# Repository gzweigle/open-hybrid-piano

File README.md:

# Hybrid MIDI Digital Piano

Also known as **stem piano**

## How to Build A Hybrid Piano
Go straight to the [pianos/](pianos/) directory!

But first, please read the [WARNINGS](WARNINGS.md) and [HELP](HELP.md) files that are located in this root directory.

See the [STATUS](STATUS.md) file for status of the project and repository.

If you would like to contribute hardware, software, mechanical, or firmware to the project, see the [CONTRIBUTING](CONTRIBUTING.md) file.

**If you build a piano, please share about it in the Show & Tell Discussions of this repository.**

## Overview

A hybrid piano combines the physical action of an acoustic piano with MIDI, sound generation, and other features of a digital keyboard. Some piano manufacturers sell hybrid pianos.

This project ("*stem piano*") is an open-source hybrid digital piano.

The qualifier digital is important. It means that signals are sampled with an analog-to-digital converter (ADC) and then all processing is with a microprocessor. Therefore, once the hardware is installed all algorithms, improvements, and new features are with software or firmware.

The repository includes schematics, printed circuit board layouts, firmware source files for the real-time processing, optional software source files for Ethernet connected features, and lists of required hardware components.

A physical piano action, or other instrument, is required. The electronics and code (*stem piano*) will work with a grand or upright piano action. Mechanical suggestions are included but not detailed mechanical instructions.

The platform and code could also adapt to building a range of other unique and innovative musical instruments.

## Directory Organization

The components required to build a piano are located in the [firmware/](firmware/), [hardware/](hardware/), [mechanical/](mechanical/) and [software/](software/) directories. In each directory is a *research* subdirectory and a *releases* subdirectory.

Each *research* subdirectory contains code and hardware for work in progress. It could have major bugs. It could be incomplete.

Each *releases* subdirectory contains code and hardware ready for use. The material in *releases* could partially duplicate material in one or more *research* subdirectories. However, the requirement is that anything in *releases* is well-tested, complete, and ready-to-use.

More details on each directory:

#### [design/](design/)

Designs and engineering analysis. To keep the repository small, associated data may be located in the separate Piano-Data repository.

#### [documentation/](documentation/)

High level documentation.

Includes [documentation/video_documentation.md](documentation/video_documentation.md) for historical, how-to, and other documentation in video form.

#### [pianos/](pianos/)

Building a complete piano requires firmware, hardware, mechanical, and sometimes software. The *pianos/* directory provides information on everything needed to build a specific version of a musical instrument.

Best place to start for learning the firmware, software, mechanical, and hardware.

#### [firmware/](firmware/)

Real-time code running on custom hardware from *hardware/* directory.

#### [hardware/](hardware/)

All printed circuit boards and related parts and design. A separate open-source license for the hardware is in this directory and applies to all hardware.

#### [mechanical/](mechanical/)

Anything to physically build a piano. A separate open-source license for mechanical is in this directory and applies to anything mechanical.

#### [software/](software/)

Code running on a standard computer or Raspberry Pi connected to the piano over Ethernet or MIDI.

## Repositories

#### (1) Original

This "DIY" repository. Organized per above.

#### (2) Stem Piano

https://github.com/stem-piano

Experimenting with a GitHub organization. The documentation and links for building individual pianos is here. Links are back to this original "DIY" repository.

May or may not migrate all files in the future. To be decided in the future.

## Related Projects:

Work was inspired, in part, by https://github.com/ekumanov/cybrid

See also:

* https://github.com/jkominek/piano-conversion/
* https://github.com/davidedelvento/Mybrid
* https://www.youtube.com/watch?v=nRBsudMpwwc
* https://www.youtube.com/watch?v=-kpf0OSJxkE
* https://www.youtube.com/watch?v=b-PRGymqECM

## "stem piano" because?

* science technology engineering math
* like a plant stem, everything here is one component of the overall instrument
* like a note stem, everything here is one component of...
* 12 leaves on the logo, matches 12 piano notes
* logo looks like a sine wave
* sounds cool
* does not sound cool

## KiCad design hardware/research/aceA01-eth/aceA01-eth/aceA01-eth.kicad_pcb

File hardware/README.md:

# Stem Piano Hardware
See [kicad_general.md](./kicad_general.md) in this directory for information on the libraries.

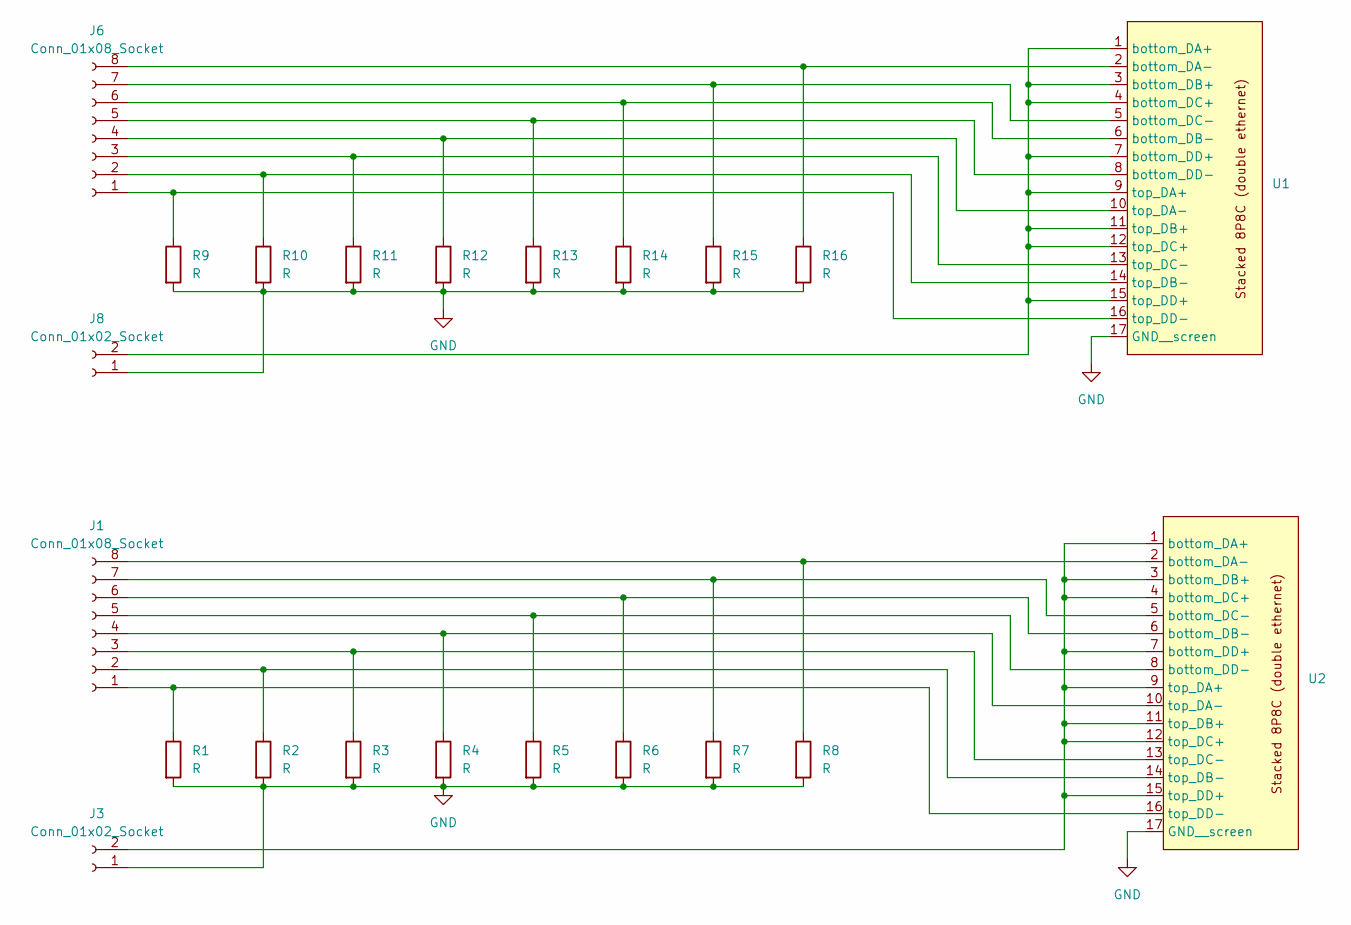
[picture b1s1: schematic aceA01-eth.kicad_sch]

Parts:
J1: Conn_01x08_Socket; PinSocket_1x08_P2.54mm_Vertical
J3, J8: Conn_01x02_Socket; PinSocket_1x02_P2.54mm_Vertical_SMD_Pin1Right
J6: Conn_01x08_Socket; PinSocket_1x08_P2.54mm_Vertical_SMD_Pin1Left
R1, R2, R3, R4, R5, R6, R7, R8, R9, R10, R11, R12, R13, R14, R15, R16: R; R_0805_2012_1.20x1.40mm_medpad
U1: Stacked8P8C_noFrontPins
U2: Stacked8P8C

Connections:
GND: J3.1, J8.1, R1.2, R2.2, R3.2, R4.2, R5.2, R6.2, R7.2, R8.2, R9.2, R10.2, R11.2, R12.2, R13.2, R14.2, R15.2, R16.2, U1.17 (GND__screen), U2.17 (GND__screen)
unnamed: J1.1, R1.1, U2.16 (top_DD-)
unnamed: J1.2, R2.1, U2.14 (top_DB-)
unnamed: J1.3, R3.1, U2.13 (top_DC-)
unnamed: J1.4, R4.1, U2.10 (top_DA-)
unnamed: J1.5, R5.1, U2.8 (bottom_DD-)
unnamed: J1.6, R6.1, U2.6 (bottom_DB-)
unnamed: J1.7, R7.1, U2.5 (bottom_DC-)
unnamed: J1.8, R8.1, U2.2 (bottom_DA-)
unnamed: J3.2, U2.1 (bottom_DA+), U2.3 (bottom_DB+), U2.4 (bottom_DC+), U2.7 (bottom_DD+), U2.9 (top_DA+), U2.11 (top_DB+), U2.12 (top_DC+), U2.15 (top_DD+)
unnamed: J6.1, R9.1, U1.16 (top_DD-)
unnamed: J6.2, R10.1, U1.14 (top_DB-)
unnamed: J6.3, R11.1, U1.13 (top_DC-)
unnamed: J6.4, R12.1, U1.10 (top_DA-)
unnamed: J6.5, R13.1, U1.8 (bottom_DD-)
unnamed: J6.6, R14.1, U1.6 (bottom_DB-)
unnamed: J6.7, R15.1, U1.5 (bottom_DC-)
unnamed: J6.8, R16.1, U1.2 (bottom_DA-)
unnamed: J8.2, U1.1 (bottom_DA+), U1.3 (bottom_DB+), U1.4 (bottom_DC+), U1.7 (bottom_DD+), U1.9 (top_DA+), U1.11 (top_DB+), U1.12 (top_DC+), U1.15 (top_DD+)

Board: 2 copper layers, 22 parts (20 on the bottom side), 19 nets, no tracks yet.

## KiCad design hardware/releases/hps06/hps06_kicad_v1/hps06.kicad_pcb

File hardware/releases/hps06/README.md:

# Hammer Position Sensor (HPS) Version 0.6

## Introduction

Originally, the HPS PCB was for hammers.  However, the sensor also works for dampers.  Not changing the name because many circuit boards have already been built.

This circuit board includes a trimming resistor. Unless needed for a specific use case, the circuit board with trimming resistor is not recommended.

In repository for historical reasons.

## Features

### I/O
* Power input.
* Analog output signal, with range set by resistors.
* Ground.

### Size
* 1.5 inches long.
* 0.4 inches wide.

### Capabilities
* CNY70 sensor.
* Trimming resistor to fine tune output voltage maximum value.
* All resistors are surface mount packages.

### Pin Order:
* Power
* Signal
* Ground

## Calibrating

Adjust the RV0 trimming resistor to get the output voltage in the correct range. A 1.0mm flathead screwdriver is required. Turn the screw slowly and gently. Information according to the datasheet [Bourns 3224 - 4mm SMD Trimpot Trimming Potentiometer, C1753 5/17/18]:
* Adjustment angle = 12 turns.
* Rotational cycling max = 200 cycles.

Based on testing, typical adjustment is no more than approximately 2 turns clockwise or counterclockwise. This results in a resistance range of approximately 75 to 125 ohms.

Turning the RV0 trimming screw clockwise decreases the resistance between pins 2 and 3 of the trimming resistor RV0 ==> this decreases the combined resistance R1 + RV0 ==> this increases the forward current of the CNY-70 emitter ==> this increases the output voltage.

Turning the RV0 trimming screw counterclockwise increases the resistance between pins 2 and 3 of the trimming resistor RV0 ==> this increases the combined resistance R1 + RV0 ==> this decreases the forward current of the CNY-70 emitter ==> this decreases the output voltage.

R2 sets the maximum output voltage. If the output voltage is too large, the analog-to-digital converter will clip. If the output voltage is smaller, it decreases the dynamic range. The piano will work with a lower dynamic range but may not work if the signal is clipping. Therefore, if the R2 value in bill of materials is unavailable, choose a smaller value.

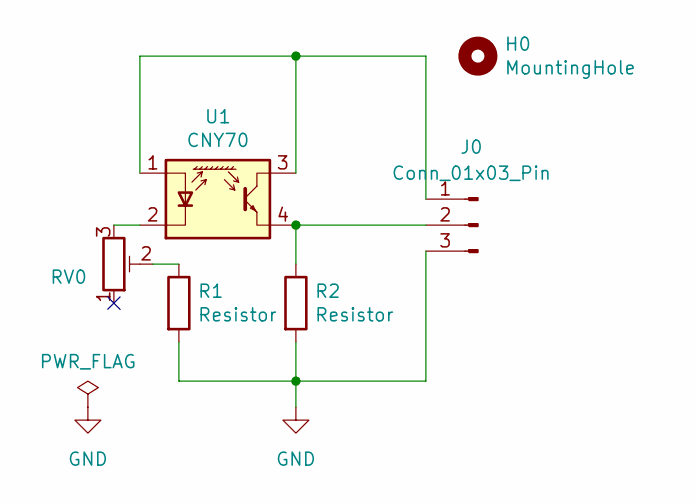
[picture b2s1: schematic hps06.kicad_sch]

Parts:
H0: MountingHole; MountingHole_3.5mm_Pad_TopBottom
J0: Conn_01x03_Pin; PinHeader_1x03_P2.54mm_Vertical
R1, R2: Resistor; R_0805_2012_1.20x1.40mm_bigpad
RV0: R_Potentiometer_Trim; Bourns_3224X_Vertical_bigpads
U1: CNY70; Vishay_CNY70

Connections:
GND: J0.3, R1.2, R2.2
unnamed: J0.1, U1.1 (A), U1.3 (C)
unnamed: J0.2, R2.1, U1.4 (E)
unnamed: R1.1, RV0.2
unnamed: RV0.3, U1.2 (K)

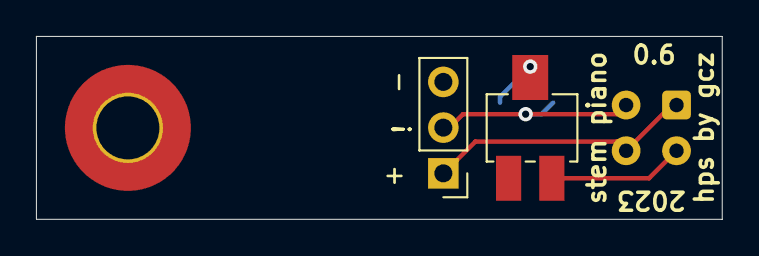
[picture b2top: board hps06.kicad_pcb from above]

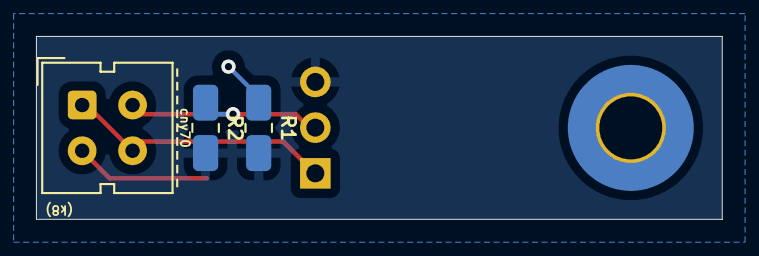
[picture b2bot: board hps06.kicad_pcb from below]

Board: 2 copper layers, 38.1 x 10.2 mm, 6 parts (3 on the bottom side), 5 nets.

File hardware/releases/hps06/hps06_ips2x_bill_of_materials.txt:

Label,   Description,           Package,    Part Number,          Required?,     Est Cost,     Comment
-,       HPS 0.6 circuit board, -,          -,                    Yes,           1.00,        -
RV0,     Trimmer, 200 ohm,      -,          3224X-1-201E,         Yes,           5.00,        -
R1,      50 ohm resistor,       0805,       CRCW080550R0FKTA,     Yes,           0.25,        0.125W. 5% tolerance or better. On back of PCB.
R2,      4120 ohm resistor,     0805,       ERA-6AEB4121V,        Yes,           0.25,        0.125W. 5% tolerance or better. On back of PCB.
U1,      CNY70 optical sensor,  -,          CNY70,                Yes,           1.00,        On back of PCB.
J0,      1x3 pin male 0.1in,    -,          -,                    Yes,           0.06,        -

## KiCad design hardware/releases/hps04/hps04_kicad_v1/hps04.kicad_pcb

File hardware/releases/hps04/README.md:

# Hammer Position Sensor (HPS) Version 0.4

## Introduction

Originally, the HPS PCB was for hammers.  However, the sensor also works for dampers.  Not changing the name because many circuit boards have already been built.

## Features

### I/O
* Power input.
* Analog output signal, with range set by resistors.
* Ground.

### Size
* 1.5 inches long.
* 0.4 inches wide.

### Capabilities
* CNY70 sensor.
* Fixed resistors.
* All resistors are through hole.

### Pin Order:
* Power
* Signal
* Ground

## Resistors

R2 sets the maximum output voltage. If the output voltage is too large, the analog-to-digital converter will clip. If the output voltage is smaller, it decreases the dynamic range. The piano works with a lower dynamic range but may not work if the signal is clipping. Therefore, if the R2 value in bill of materials is unavailable, choose a smaller value. If the R1 value is unavailable, choose a larger value.

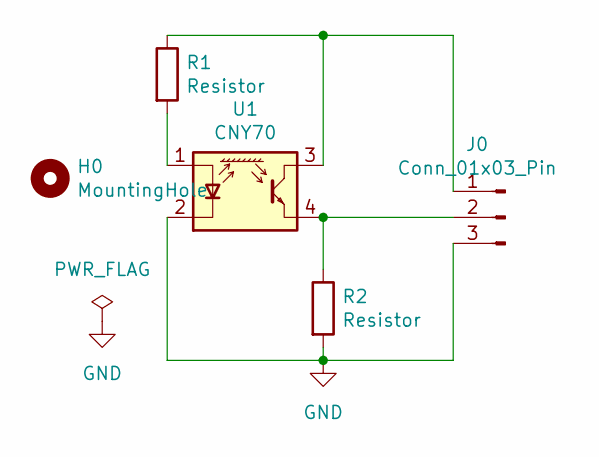
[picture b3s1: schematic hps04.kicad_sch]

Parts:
H0: MountingHole; MountingHole_3.5mm_Pad_TopBottom
J0: Conn_01x03_Pin; PinHeader_1x03_P2.54mm_Vertical
R1, R2: Resistor; R_Axial_DIN0204_L3.6mm_D1.6mm_P7.62mm_Horizontal
U1: CNY70; Vishay_CNY70

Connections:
GND: J0.3, R2.2, U1.2 (K)
unnamed: J0.1, R1.1, U1.3 (C)
unnamed: J0.2, R2.1, U1.4 (E)
unnamed: R1.2, U1.1 (A)

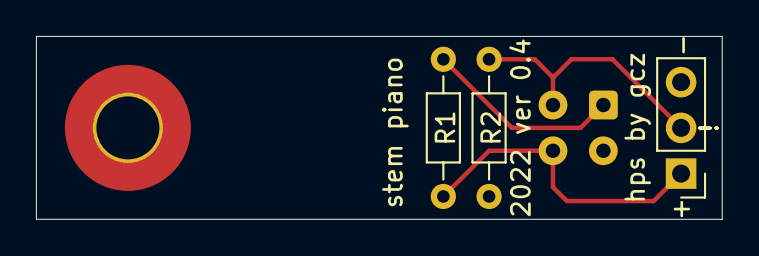
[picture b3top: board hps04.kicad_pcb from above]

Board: 2 copper layers, 38.1 x 10.2 mm, 5 parts (1 on the bottom side), 4 nets.

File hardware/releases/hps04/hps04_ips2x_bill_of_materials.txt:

Label,   Description,           Package,       Part Number,      Required?,     Est Cost,     Comment
-,       HPS 0.4 circuit board, -,             -,                Yes,           1.00,        -
R1,      50 ohm resistor,       through hole,  -,                Yes,           0.05,        0.125W. 5% tolerance or better.
R2,      4100 ohm resistor,     through hole,  -,                Yes,           0.05,        This value or slightly smaller.
U1,      CNY70 optical sensor,  -,             CNY70,            Yes,           1.00,        -
J0,      1x3 pin male 0.1in,    -,             -,                Yes,           0.06,        -

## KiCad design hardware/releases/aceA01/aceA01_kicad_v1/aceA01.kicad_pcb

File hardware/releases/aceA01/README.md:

# Analog Condition Equalize (ACE) "A" - Version 0.1

Identical to ACE A 0.0 with the following changes:
* Removed ground plane because it makes soldering more difficult (thermal) and adds little benefit.
* For headers placed on back of board, corrected the footprints to match.
* Adjusted some of the footprint label locations.

No functional changes.

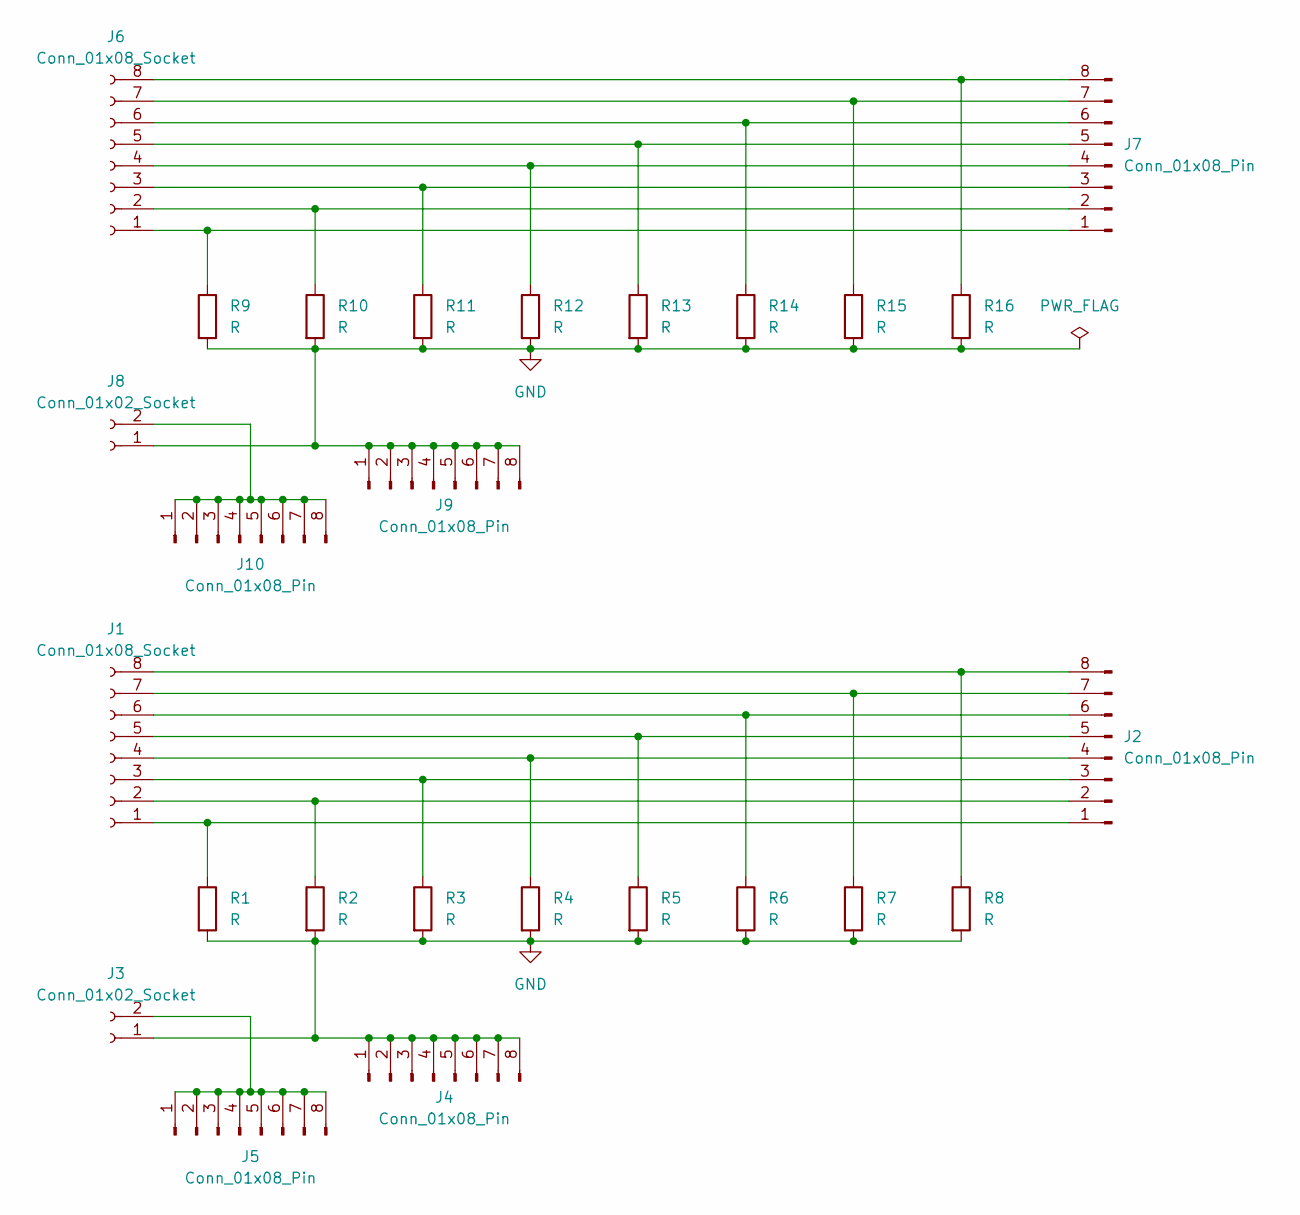
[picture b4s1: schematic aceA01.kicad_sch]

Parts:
J1, J6: Conn_01x08_Socket; PinSocket_1x08_P2.54mm_Vertical
J2, J4, J5, J7, J9, J10: Conn_01x08_Pin; PinHeader_1x08_P2.54mm_Vertical
J3, J8: Conn_01x02_Socket; PinSocket_1x02_P2.54mm_Vertical
R1, R2, R3, R4, R5, R6, R7, R8, R9, R10, R11, R12, R13, R14, R15, R16: R; R_0805_2012_1.20x1.40mm_medpad

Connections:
GND: J3.1, J4.1, J4.2, J4.3, J4.4, J4.5, J4.6, J4.7, J4.8, J8.1, J9.1, J9.2, J9.3, J9.4, J9.5, J9.6, J9.7, J9.8, R1.2, R2.2, R3.2, R4.2, R5.2, R6.2, R7.2, R8.2, R9.2, R10.2, R11.2, R12.2, R13.2, R14.2, R15.2, R16.2
unnamed: J1.1, J2.1, R1.1
unnamed: J1.2, J2.2, R2.1
unnamed: J1.3, J2.3, R3.1
unnamed: J1.4, J2.4, R4.1
unnamed: J1.5, J2.5, R5.1
unnamed: J1.6, J2.6, R6.1
unnamed: J1.7, J2.7, R7.1
unnamed: J1.8, J2.8, R8.1
unnamed: J3.2, J5.1, J5.2, J5.3, J5.4, J5.5, J5.6, J5.7, J5.8
unnamed: J6.1, J7.1, R9.1
unnamed: J6.2, J7.2, R10.1
unnamed: J6.3, J7.3, R11.1
unnamed: J6.4, J7.4, R12.1
unnamed: J6.5, J7.5, R13.1
unnamed: J6.6, J7.6, R14.1
unnamed: J6.7, J7.7, R15.1
unnamed: J6.8, J7.8, R16.1
unnamed: J8.2, J10.1, J10.2, J10.3, J10.4, J10.5, J10.6, J10.7, J10.8

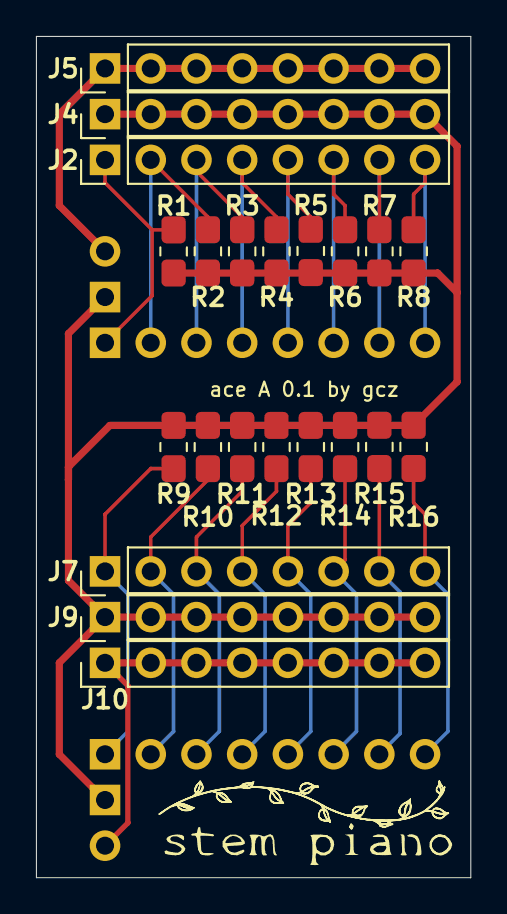
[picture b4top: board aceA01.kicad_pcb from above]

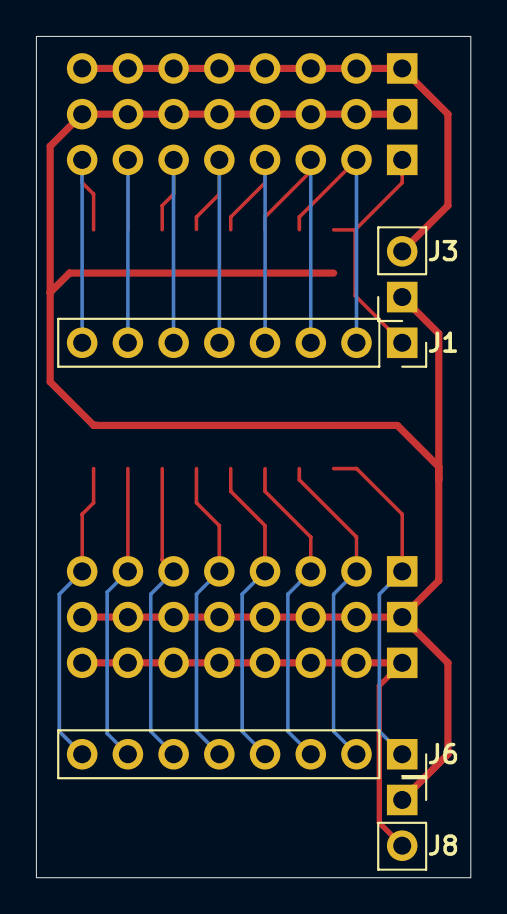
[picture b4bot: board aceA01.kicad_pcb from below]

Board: 2 copper layers, 24.1 x 46.7 mm, 26 parts (4 on the bottom side), 19 nets.

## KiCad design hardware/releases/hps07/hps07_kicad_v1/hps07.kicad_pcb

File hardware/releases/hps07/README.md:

# Hammer Position Sensor (HPS) Version 0.7

## Introduction

Originally, the HPS PCB was for hammers.  However, the sensor also works for dampers.  Not changing the name because many circuit boards have already been built.

Version 0.7 is the same as version 0.6 except with a different header pin order. This provides a better physical match to some mainboards.

This circuit board includes a trimming resistor. Unless needed for a specific use case, the circuit board with trimming resistor is not recommended.

## Features

### I/O
* Power input.
* Ground.
* Analog output signal, with range set by resistors.

### Size
* 1.5 inches long.
* 0.4 inches wide.

### Capabilities
* CNY70 sensor.
* Trimming resistor to fine tune output voltage maximum value.
* All resistors are surface mount packages.

### Pin Order:
* Power
* Ground
* Signal

## Calibrating

### Overview

Adjust the RV0 trimming resistor to get the output voltage in the correct range. A 1.0mm flathead screwdriver is required. Turn the screw slowly and gently. Information according to the datasheet [Bourns 3224 - 4mm SMD Trimpot Trimming Potentiometer, C1753 5/17/18]:
* Adjustment angle = 12 turns.
* Rotational cycling max = 200 cycles.

Based on testing, typical adjustment is no more than approximately 2 turns clockwise or counterclockwise. This results in a resistance range of approximately 70 to 130 ohms.

Turning the RV0 trimming screw clockwise decreases the resistance between pins 2 and 3 of the trimming resistor RV0 ==> this decreases the combined resistance R1 + RV0 ==> this increases the forward current of the CNY-70 emitter ==> this increases the output voltage.

Turning the RV0 trimming screw counterclockwise increases the resistance between pins 2 and 3 of the trimming resistor RV0 ==> this increases the combined resistance R1 + RV0 ==> this decreases the forward current of the CNY-70 emitter ==> this decreases the output voltage.

### Experimental Data

Each CNY-70 is different. The following data is for randomly selected CNY-70.

Tests are with the following resistance values.
* R1 = 50 ohms
* R2 = 4300 ohms

In the following table, *screw turns* definition:
* (+) is clockwise
* (-) is counterclockwise
* 1 = a full, 360 degree turn
* 0.5 = a half, 180 degree turn

The trimmer RV0 is 200 ohms. The nominal value is 100 ohms. The nominal value is most likely the initial value when the trimmer is purchased. All *screw turns* are referenced to the nominal. For accurate results, check with an ohmmeter.

| screw turns | RV0 | current (mA) | maximum output voltage |
|-------------|-----|--------------|------------------------|
| + 2.5       |  53 | 18.5         | 3.10                   | 
| + 2.0       |  62 | 17           | 3.05                   | 
| + 1.5       |  71 | 16           | 2.85                   | 
| + 1.0       |  81 | 14.5         | 2.60                   | 
| + 0.5       |  93 | 13           | 2.35                   | 
| 0           | 105 | 12           | 2.18                   | 
| - 0.5       | 116 | 11           | 2.05                   | 
| - 1.0       | 126 | 10           | 1.90                   | 
| - 1.5       | 135 | 10           | 1.50                   | 

R2 sets the maximum output voltage. If the output voltage is too large, the analog-to-digital converter will clip. If the output voltage is smaller, it decreases the dynamic range. The piano will work with a lower dynamic range but may not work if the signal is clipping. Therefore, if the R2 value in bill of materials is unavailable, choose a smaller value.

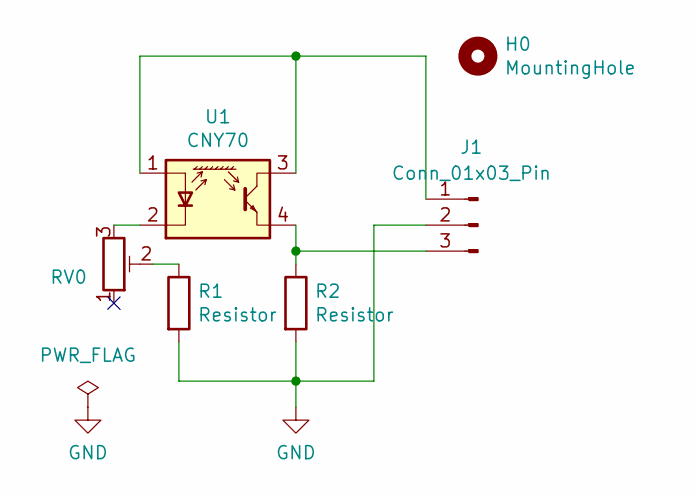
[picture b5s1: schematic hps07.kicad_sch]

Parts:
H0: MountingHole; MountingHole_3.5mm_Pad_TopBottom
J1: Conn_01x03_Pin; PinHeader_1x03_P2.54mm_Vertical
R1, R2: Resistor; R_0805_2012_1.20x1.40mm_bigpad
RV0: R_Potentiometer_Trim; Bourns_3224X_Vertical_bigpads
U1: CNY70; Vishay_CNY70

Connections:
GND: J1.2, R1.2, R2.2
unnamed: J1.1, U1.1 (A), U1.3 (C)
unnamed: J1.3, R2.1, U1.4 (E)
unnamed: R1.1, RV0.2
unnamed: RV0.3, U1.2 (K)

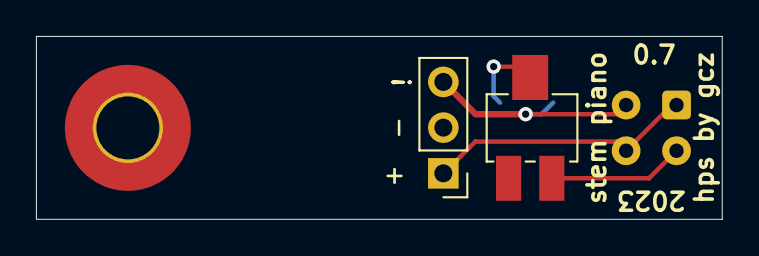
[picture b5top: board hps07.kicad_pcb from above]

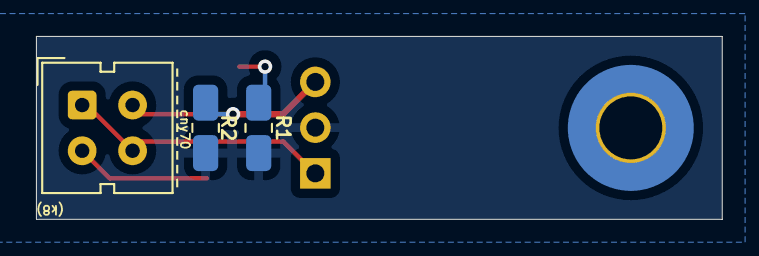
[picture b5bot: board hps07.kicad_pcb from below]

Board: 2 copper layers, 38.1 x 10.2 mm, 6 parts (3 on the bottom side), 5 nets.

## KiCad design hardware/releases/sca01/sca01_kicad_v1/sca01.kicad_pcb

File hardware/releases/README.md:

# Hardware Releases

All released hardware is located in this directory.

See [../kicad_general.md](../kicad_general.md) for more information on KiCad files.

## Manufacturing

### Gerber Files

To manufacture a circuit board, send the files in a *_gerber/ folder to a PCB manufacturer. Board fabrication and test is always with the *_gerber/ folder files.

If the circuit board directory does not include a *_gerber/ folder, this means the boards have not been fully fabricated and tested. In this case, use the KiCad project. Once tested, add a *_gerber/ folder and files.

### KiCad Project Files

Boards for Gerber files were fabricated and tested.

Each directory of KiCad project files end with a "KiCad files" _v* version number. The KiCad libraries directories in this repository also end with the same "KiCad Files" _v* version number. Use the KiCad libraries directory with the same "KiCad files" _v* version number as the KiCad project files directories.

The "KiCad files" _v* version number system is a different numbering system than the KiCad program version and is different than the circuit board version. A unique "KiCad files" _v* version number for the KiCad directories allows flexible updates with anything related to KiCad changes.

### Components

Each bill of materials file ends with a number. This number allows different component variants for the same board. Piano building instructions will specify the bill of materials variant.

For any discrepancy between schematic and bill of materials, use the bill of materials. This includes part values as well as whether a through-hole component is placed on front or back of a circuit board.

## Numbering Systems Summary

* Circuit board version. Each circuit board version is in its own unique subdirectory.
* Bill of materials. The number on each bill of materials is for a board variant. Instructions for building each piano will specify the correct bill of materials variant.
* KiCad files _v* version number. Use this number to match KiCad files with the symbol and footprint library files in this repository.
* KiCad program version. If a circuit board directory includes multiple KiCad program versions, the circuit boards may have a silkscreen label indicating the KiCad program version used for fabrication.

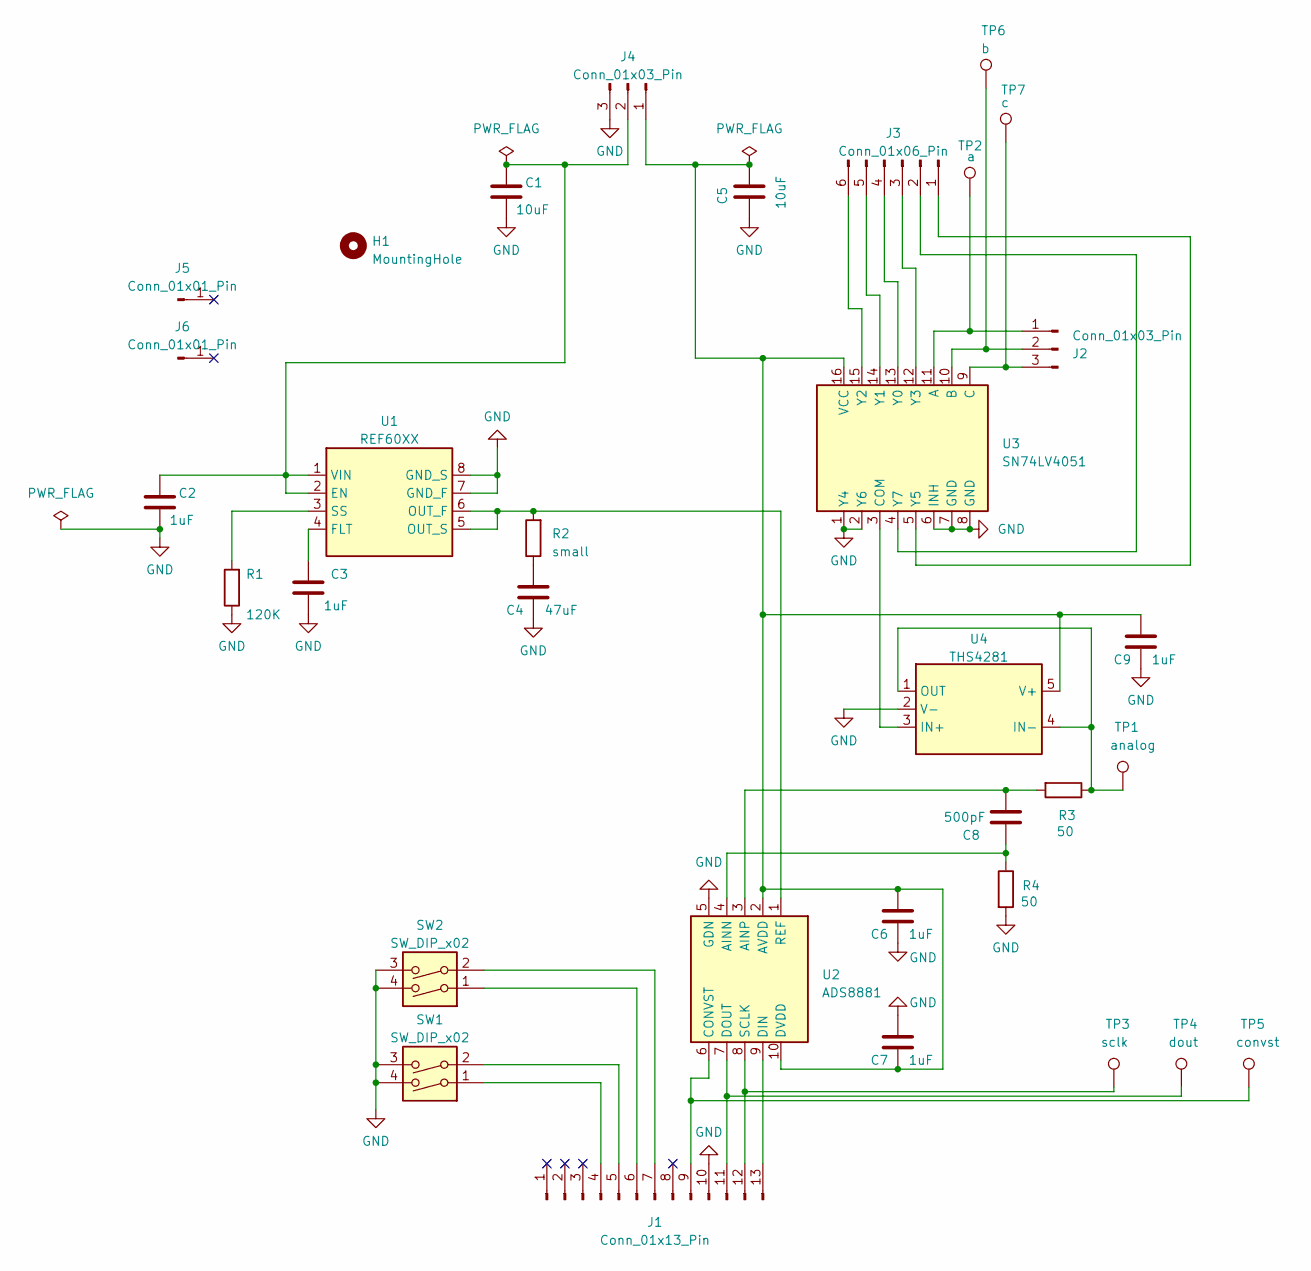
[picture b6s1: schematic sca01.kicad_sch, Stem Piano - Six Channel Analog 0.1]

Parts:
C1, C5: 10uF; C_0805_2012_1.18x1.45mm_medpad
C2, C3, C6, C7, C9: 1uF; C_0805_2012_1.18x1.45mm_medpad
C4: 47uF; C_0805_2012_1.18x1.45mm_medpad
C8: 500pF; C_0805_2012_1.18x1.45mm_medpad
H1: MountingHole; MountingHole_2.2mm_M2_DIN965_Pad_TopBottom
J1: Conn_01x13_Pin; PinHeader_1x13_P2.54mm_Vertical
J2, J4: Conn_01x03_Pin; PinHeader_1x03_P2.54mm_Vertical
J3: Conn_01x06_Pin; PinHeader_1x06_P2.54mm_Vertical
J5, J6: Conn_01x01_Pin; PinHeader_1x01_P2.54mm_Vertical
R1: 120K; R_0805_2012_1.20x1.40mm_medpad
R2: small; R_0805_2012_1.20x1.40mm_medpad
R3, R4: 50; R_0805_2012_1.20x1.40mm_medpad
SW1, SW2: SW_DIP_x02; SW_DIP_SPSTx02_Slide_medpad
TP1: analog; TestPoint_Keystone_5000-5004_Miniature
TP2: a; TestPoint_Keystone_5000-5004_Miniature
TP3: sclk; TestPoint_Keystone_5000-5004_Miniature
TP4: dout; TestPoint_Keystone_5000-5004_Miniature
TP5: convst; TestPoint_Keystone_5000-5004_Miniature
TP6: b; TestPoint_Keystone_5000-5004_Miniature
TP7: c; TestPoint_Keystone_5000-5004_Miniature
U1: REF60XX; VSSOP-8_3.0x3.0mm_P0.65mm_medpads
U2: ADS8881; VSSOP-10_medpad
U3: SN74LV4051; SOIC-16_3.9x9.9mm_P1.27mm_medpad
U4: THS4281; SOT-23-5_medpad

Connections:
GND: C1.2, C2.2, C3.1, C4.1, C5.2, C6.1, C7.2, C9.1, J1.10, J4.3, R1.1, R4.2, SW1.3, SW1.4, SW2.3, SW2.4, U1.7 (GND_F), U1.8 (GND_S), U2.5 (GDN), U3.1 (Y4), U3.2 (Y6), U3.6 (INH), U3.7 (GND), U3.8 (GND), U4.2 (V-)
unnamed: C4.2, R2.1
unnamed: J1.4, SW1.1
unnamed: J1.5, SW1.2
unnamed: J1.6, SW2.1
unnamed: J1.7, SW2.2
unnamed: J1.9, TP5.1, U2.6 (CONVST)
unnamed: J1.11, TP4.1, U2.7 (DOUT)
unnamed: J1.12, TP3.1, U2.8 (SCLK)
unnamed: J1.13, U2.9 (DIN)
unnamed: J2.1, TP2.1, U3.11 (A)
unnamed: J2.2, TP6.1, U3.10 (B)
unnamed: J2.3, TP7.1, U3.9 (C)
unnamed: J3.1, U3.5 (Y5)
unnamed: J3.2, U3.4 (Y7)
unnamed: J3.3, U3.12 (Y3)
unnamed: J3.4, U3.13 (Y0)
unnamed: J3.5, U3.14 (Y1)
unnamed: J3.6, U3.15 (Y2)
unnamed: C5.1, C6.2, C7.1, C9.2, J4.1, U2.2 (AVDD), U2.10 (DVDD), U3.16 (VCC), U4.5 (V+)
unnamed: C1.1, C2.1, J4.2, U1.1 (VIN), U1.2 (EN)
unnamed: C3.2, U1.4 (FLT)
unnamed: R2.2, U1.5 (OUT_S), U1.6 (OUT_F), U2.1 (REF)
unnamed: R1.2, U1.3 (SS)
unnamed: C8.1, R4.1, U2.4 (AINN)
unnamed: C8.2, R3.2, U2.3 (AINP)
unnamed: U3.3 (COM), U4.3 (IN+)
unnamed: R3.1, TP1.1, U4.1 (OUT), U4.4 (IN-)

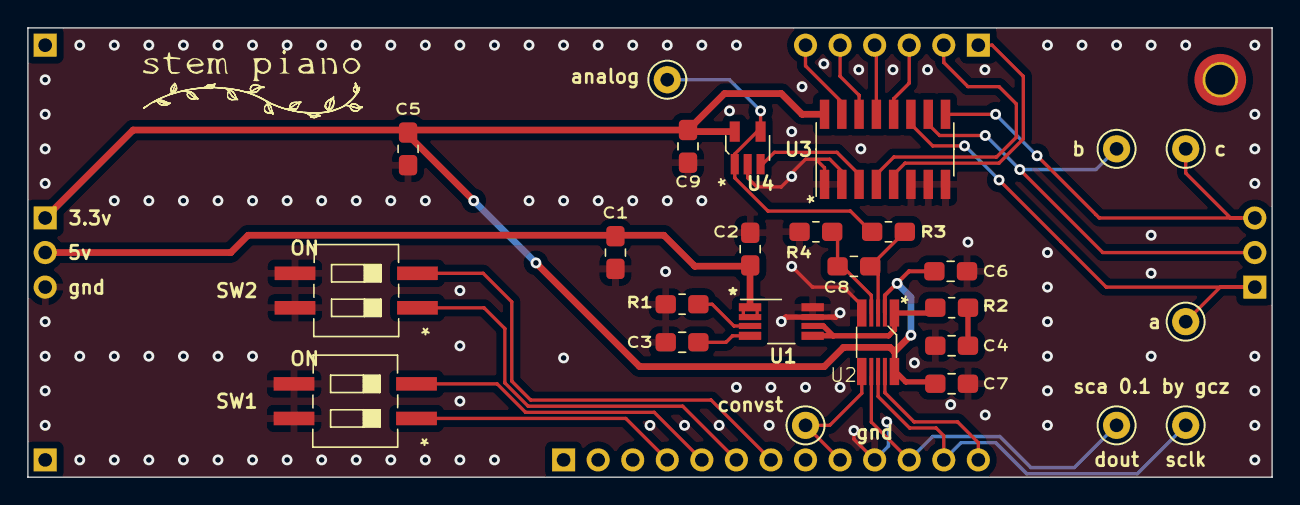
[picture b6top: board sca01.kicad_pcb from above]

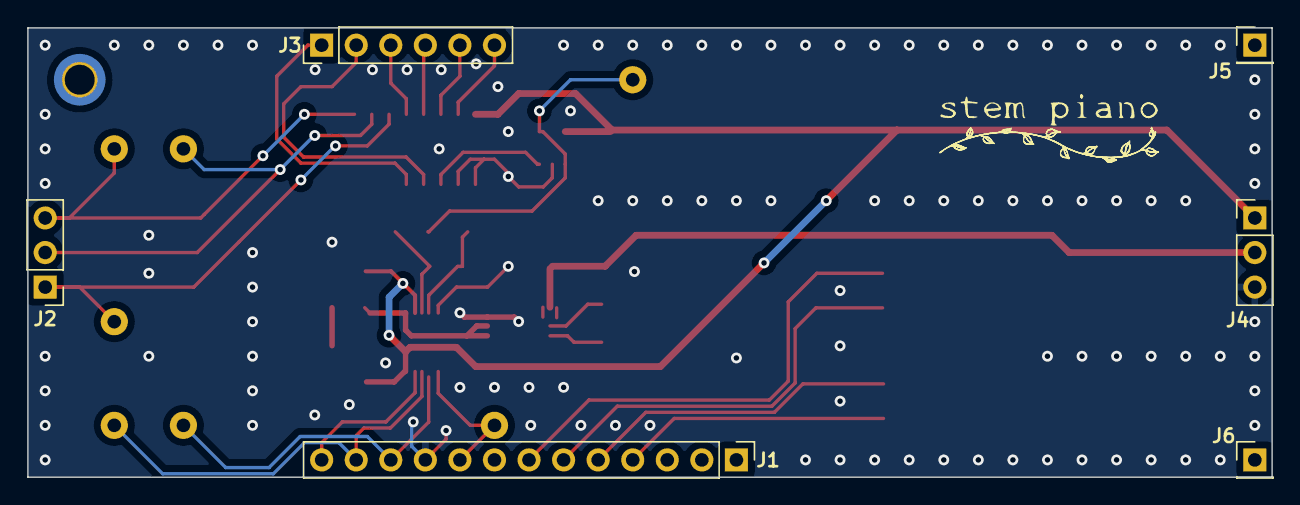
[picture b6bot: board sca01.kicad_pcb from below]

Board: 2 copper layers, 91.4 x 33.0 mm, 33 parts (6 on the bottom side), 28 nets.

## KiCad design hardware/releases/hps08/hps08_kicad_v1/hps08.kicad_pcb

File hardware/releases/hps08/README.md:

# Hammer Position Sensor (HPS) Version 0.8

## Introduction

Originally, the HPS PCB was for hammers.  However, the sensor also works for dampers.  Not changing the name because many circuit boards have already been built.

Like version 0.4, version 0.8 has fixed resistor values. Version 0.8 is a different header pin order compared to version 0.4. This provides a better physical match to some mainboards.

Version 0.4 is through hole resistors, version 0.8 is surface mount resistors.

## Features

### I/O
* Power input.
* Ground.
* Analog output signal, with range set by resistors.

### Size
* 1.5 inches long.
* 0.4 inches wide.

### Capabilities
* CNY70 sensor.
* All resistors are surface mount packages.

### Pin Order:
* Power
* Ground
* Signal

## Specifications

Current is approximately 11 milliamps.

Because of CNY-70 tolerances each HPS 0.8 board has a different maximum output voltage. The maximum output voltage is when the distance from the CNY-70 on the HPS 0.8, to a white reflective surface, is at approximately 1 millimeter.

Test results:
* The board to board maximum output voltage ranges from 1.5 volts to 2.5 volts.
* The board to board average maximum output voltage is approximately 2 volts.

The maximum output voltage for each HPS 0.8 board individually does not vary. So, for example, if an HPS 0.8 board maximum output voltage is 2.1 volts when distance is smallest, the maximum output voltage is consistently 2.1 volts each time the distance is smallest.

## Resistors

R1 and R2 set the maximum output voltage. If the output voltage is too large, the analog-to-digital converter will clip. If the output voltage is smaller, it decreases the dynamic range. The piano will work with a lower dynamic range but may not work if the signal is clipping. Therefore, if the R2 value in bill of materials is unavailable, choose a smaller value. If the R1 value is unavailable, choose a larger value.

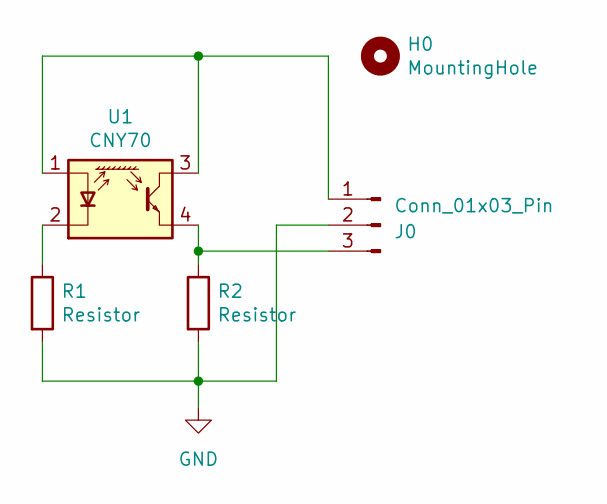
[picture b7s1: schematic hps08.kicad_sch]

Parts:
H0: MountingHole; MountingHole_3.5mm_Pad_TopBottom
J0: Conn_01x03_Pin; PinHeader_1x03_P2.54mm_Vertical
R1, R2: Resistor; R_0805_2012_1.20x1.40mm_medpad
U1: CNY70; Vishay_CNY70

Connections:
GND: J0.2, R1.2, R2.2
unnamed: J0.1, U1.1 (A), U1.3 (C)
unnamed: J0.3, R2.1, U1.4 (E)
unnamed: R1.1, U1.2 (K)

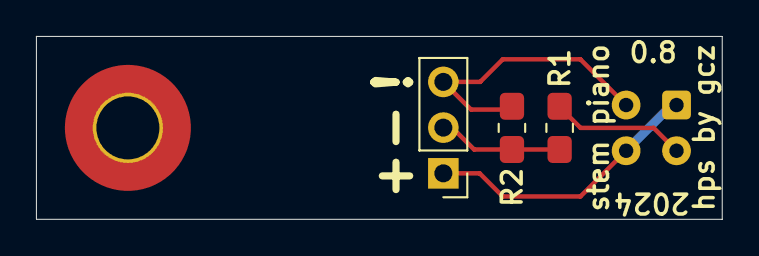
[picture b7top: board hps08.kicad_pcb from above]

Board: 2 copper layers, 38.1 x 10.2 mm, 5 parts (1 on the bottom side), 4 nets.

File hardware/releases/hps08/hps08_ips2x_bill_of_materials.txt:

Label,   Description,           Package,    Part Number,          Required?,     Est Cost,     Comment
-,       HPS 0.8 circuit board, -,          -,                    Yes,           1.00,        -
R1,      180 ohm resistor,      0805,       ERA-6AED181V,         Yes,           0.25,        0.125W. 1% tolerance or better. On back of PCB.
R2,      4300 ohm resistor,     0805,       ERA-6AEB432V,         Yes,           0.25,        0.125W. 1% tolerance or better. On back of PCB.
U1,      CNY70 optical sensor,  -,          CNY70,                Yes,           1.00,        On back of PCB.
J0,      1x3 pin male 0.1in,    -,          -,                    Yes,           0.06,        -
